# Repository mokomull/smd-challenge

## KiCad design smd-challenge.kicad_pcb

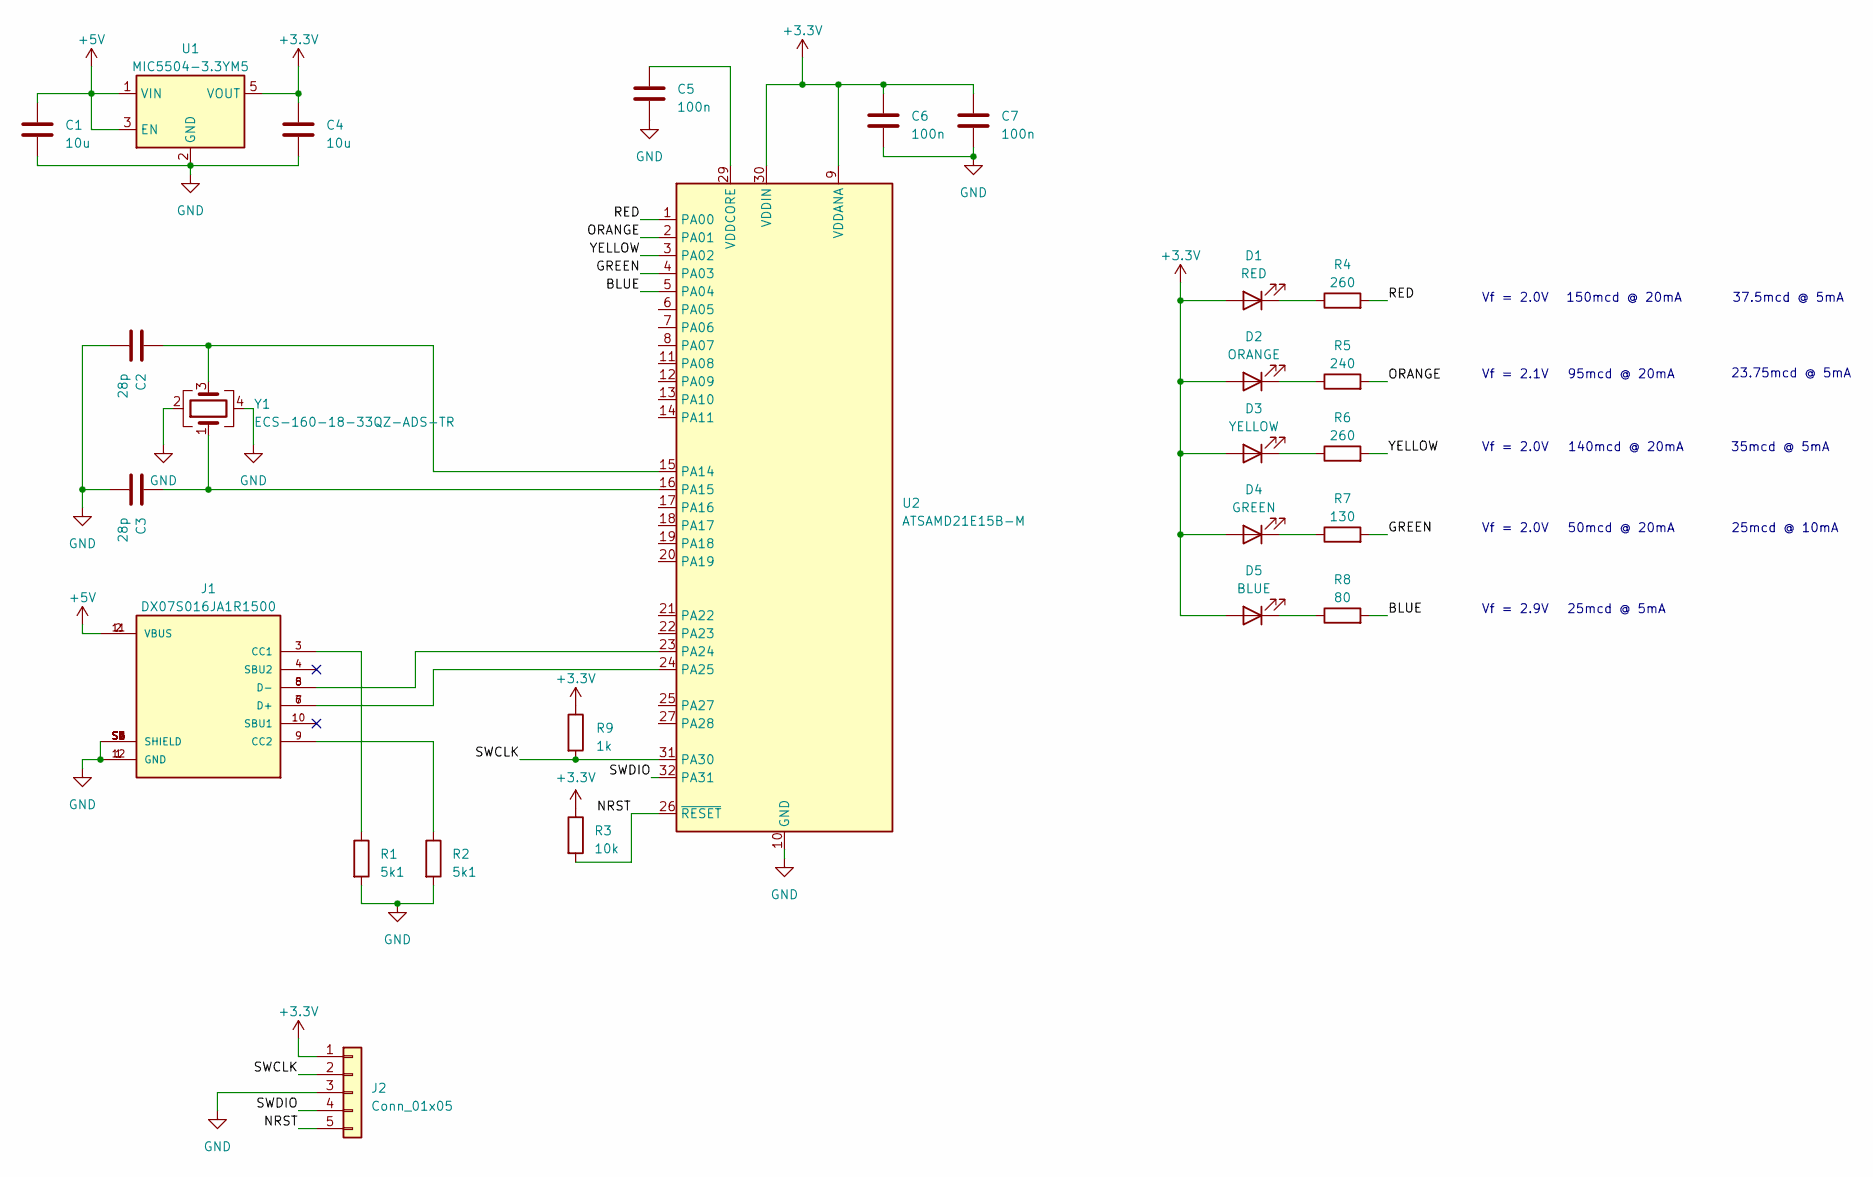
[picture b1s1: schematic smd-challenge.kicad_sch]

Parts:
C1, C4: 10u; C_1206_3216Metric; Digikey 1276-3100-1-ND
C2, C3: 28p; C_0603_1608Metric; Digikey 1276-1254-1-ND
C5, C6, C7: 100n; C_0603_1608Metric; Digikey 1276-1006-1-ND
D1: RED; LED_1206_3216Metric; Digikey 732-4991-1-ND
D2: ORANGE; LED_0805_2012Metric; Digikey 350-4355-1-ND
D3: YELLOW; LED_0603_1608Metric; Digikey 350-2032-1-ND
D4: GREEN; LED_0402_1005Metric; Digikey 732-11992-1-ND
D5: BLUE; LED_0201_0603Metric; Digikey 754-2022-1-ND
J1: DX07S016JA1R1500; JAE_DX07S016JA1R1500; PARTREV 1
J2: Conn_01x05; PinHeader_1x05_P2.54mm_Vertical_SMD_Pin1Left
R1, R2: 5k1; R_0603_1608Metric
R3: 10k; R_0603_1608Metric
R4: 260; R_1206_3216Metric; Digikey RMCF1206JT270RCT-ND
R5: 240; R_0805_2012Metric; Digikey RMCF0805JT240RCT-ND
R6: 260; R_0603_1608Metric; Digikey ‎RMCF0603JT270RCT-ND‎
R7: 130; R_0402_1005Metric; Digikey RMCF0402JT130RCT-ND
R8: 80; R_0201_0603Metric; Digikey P80.6ABCT-ND
R9: 1k; R_0603_1608Metric
U1: MIC5504-3.3YM5; SOT-23-5
U2: ATSAMD21E15B-M; QFN-32-1EP_5x5mm_P0.5mm_EP3.6x3.6mm
Y1: ECS-160-18-33QZ-ADS-TR; Crystal_SMD_SeikoEpson_FA238-4Pin_3.2x2.5mm

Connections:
+3V3: C4.1, C6.1, C7.1, D1.2 (A), D2.2 (A), D3.2 (A), D4.2 (A), D5.2 (A), J2.1, R3.1, R9.1, U1.5 (VOUT), U2.9 (VDDANA), U2.30 (VDDIN)
+5V: C1.1, J1.2 (VBUS), J1.11 (VBUS), U1.1 (VIN), U1.3 (EN)
/BLUE: R8.2, U2.5 (PA04)
/GREEN: R7.2, U2.4 (PA03)
/NRST: J2.5, R3.2, U2.26 (~RESET)
/ORANGE: R5.2, U2.2 (PA01)
/RED: R4.2, U2.1 (PA00)
/SWCLK: J2.2, R9.2, U2.31 (PA30)
/SWDIO: J2.4, U2.32 (PA31)
/YELLOW: R6.2, U2.3 (PA02)
GND: C1.2, C2.2, C3.2, C4.2, C5.2, C6.2, C7.2, J1.1 (GND), J1.12 (GND), J1.S1 (SHIELD), J1.S2 (SHIELD), J1.S3 (SHIELD), J1.S4 (SHIELD), J1.S5 (SHIELD), J1.S6 (SHIELD), J2.3, R1.2, R2.2, U1.2 (GND), U2.10 (GND), U2.28 (GND), Y1.2, Y1.4
unnamed: C2.1, U2.15 (PA14), Y1.3
unnamed: C3.1, U2.16 (PA15), Y1.1
unnamed: C5.1, U2.29 (VDDCORE)
unnamed: D1.1 (K), R4.1
unnamed: D2.1 (K), R5.1
unnamed: D3.1 (K), R6.1
unnamed: D4.1 (K), R7.1
unnamed: D5.1 (K), R8.1
unnamed: J1.3 (CC1), R1.1
unnamed: J1.5 (D-), J1.8 (D-), U2.23 (PA24)
unnamed: J1.6 (D+), J1.7 (D+), U2.24 (PA25)
unnamed: J1.9 (CC2), R2.1

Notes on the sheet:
Vf = 2.0V
Vf = 2.1V
Vf = 2.9V
25mcd @ 5mA
95mcd @ 20mA
50mcd @ 20mA
150mcd @ 20mA
140mcd @ 20mA
35mcd @ 5mA
25mcd @ 10mA
37.5mcd @ 5mA
23.75mcd @ 5mA

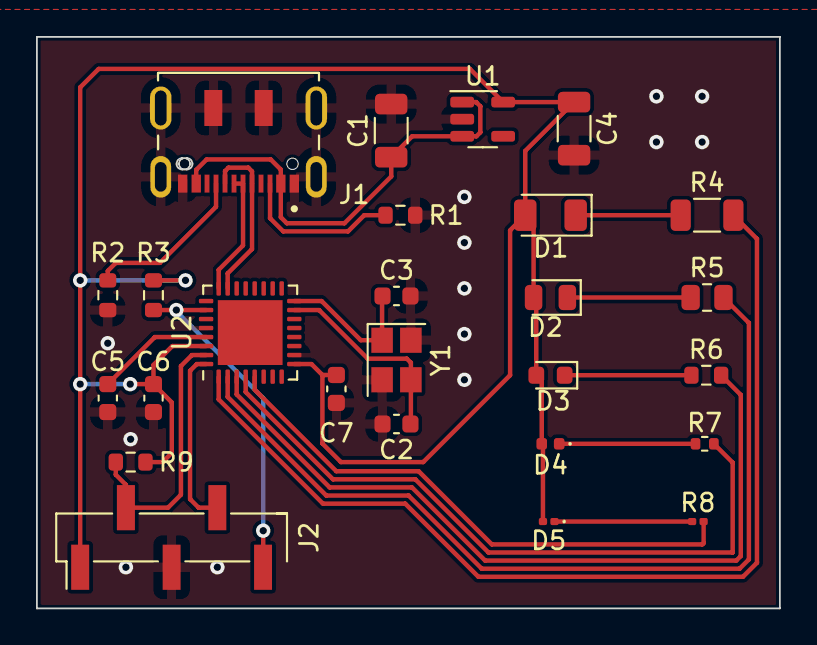
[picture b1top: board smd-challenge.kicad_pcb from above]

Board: 2 copper layers, 41.3 x 31.8 mm, 26 parts (0 on the bottom side), 23 nets.

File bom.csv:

"Source:","/home/mmullins/projects/smd-challenge/smd-challenge.kicad_sch"
"Date:","Wed 24 Mar 2021 08:59:18 PM PDT"
"Tool:","Eeschema (5.99.0-9795-gc3c3649211)"
"Generator:","/home/mmullins/Downloads/kicad/usr/share/kicad/plugins/bom_csv_grouped_by_value.py"
"Component Count:","26"

"Individual Components:"

"Item","Qty","Reference(s)","Value","LibPart","Footprint","Datasheet","Digikey","MANUFACTURER","MAXIMUM_PACKAGE_HEIGHT","PARTREV","STANDARD"
"","","C1","10u","Device:C","Capacitor_SMD:C_1206_3216Metric","~","1276-3100-1-ND","","","",""
"","","C2","12p","Device:C","Capacitor_SMD:C_0603_1608Metric","~","1276-1254-1-ND","","","",""
"","","C3","12p","Device:C","Capacitor_SMD:C_0603_1608Metric","~","1276-1254-1-ND","","","",""
"","","C4","10u","Device:C","Capacitor_SMD:C_1206_3216Metric","~","1276-3100-1-ND","","","",""
"","","C5","100n","Device:C","Capacitor_SMD:C_0603_1608Metric","~","1276-1006-1-ND","","","",""
"","","C6","100n","Device:C","Capacitor_SMD:C_0603_1608Metric","~","1276-1006-1-ND","","","",""
"","","C7","100n","Device:C","Capacitor_SMD:C_0603_1608Metric","~","1276-1006-1-ND","","","",""
"","","D1","RED","Device:LED","LED_SMD:LED_1206_3216Metric","~","732-4991-1-ND","","","",""
"","","D2","ORANGE","Device:LED","LED_SMD:LED_0805_2012Metric","~","350-4355-1-ND","","","",""
"","","D3","YELLOW","Device:LED","LED_SMD:LED_0603_1608Metric","~","350-2032-1-ND","","","",""
"","","D4","GREEN","Device:LED","LED_SMD:LED_0402_1005Metric","~","732-11992-1-ND","","","",""
"","","D5","BLUE","Device:LED","LED_SMD:LED_0201_0603Metric","~","754-2022-1-ND","","","",""
"","","J1","DX07S016JA1R1500","USBConn:DX07S016JA1R1500","USBConn6:JAE_DX07S016JA1R1500","","","JAE Industry Ltd.","3.31 mm","1","Manufacturer Recommendations"
"","","J2","Conn_01x05","Connector_Generic:Conn_01x05","Connector_PinHeader_2.54mm:PinHeader_1x05_P2.54mm_Vertical_SMD_Pin1Left","~","","","","",""
"","","R1","5k1","Device:R","Resistor_SMD:R_0603_1608Metric","~","","","","",""
"","","R2","5k1","Device:R","Resistor_SMD:R_0603_1608Metric","~","","","","",""
"","","R3","10k","Device:R","Resistor_SMD:R_0603_1608Metric","~","","","","",""
"","","R4","260","Device:R","Resistor_SMD:R_1206_3216Metric","~","RMCF1206JT270RCT-ND","","","",""
"","","R5","240","Device:R","Resistor_SMD:R_0805_2012Metric","~","RMCF0805JT240RCT-ND","","","",""
"","","R6","260","Device:R","Resistor_SMD:R_0603_1608Metric","~"," ‎RMCF0603JT270RCT-ND‎ ","","","",""
"","","R7","130","Device:R","Resistor_SMD:R_0402_1005Metric","~","RMCF0402JT130RCT-ND","","","",""
"","","R8","80","Device:R","Resistor_SMD:R_0201_0603Metric","~","P80.6ABCT-ND","","","",""
"","","R9","1k","Device:R","Resistor_SMD:R_0603_1608Metric","~","","","","",""
"","","U1","MIC5504-3.3YM5","Regulator_Linear:MIC5504-3.3YM5","Package_TO_SOT_SMD:SOT-23-5","http://ww1.microchip.com/downloads/en/DeviceDoc/MIC550X.pdf","","","","",""
"","","U2","ATSAMD21E15B-M","MCU_Microchip_SAMD:ATSAMD21E15B-M","Package_DFN_QFN:QFN-32-1EP_5x5mm_P0.5mm_EP3.6x3.6mm","http://ww1.microchip.com/downloads/en/DeviceDoc/SAM_D21_DA1_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","","","","",""
"","","Y1","FA-238 16.0000MB-K3","Device:Crystal_GND24","Crystal:Crystal_SMD_SeikoEpson_FA238-4Pin_3.2x2.5mm","~","","","","",""



"Collated Components:"

"Item","Qty","Reference(s)","Value","LibPart","Footprint","Datasheet","Digikey","MANUFACTURER","MAXIMUM_PACKAGE_HEIGHT","PARTREV","STANDARD"
"1","2","C1, C4","10u","Device:C","Capacitor_SMD:C_1206_3216Metric","~","1276-3100-1-ND","","","",""
"2","2","C2, C3","12p","Device:C","Capacitor_SMD:C_0603_1608Metric","~","1276-1254-1-ND","","","",""
"3","3","C5, C6, C7","100n","Device:C","Capacitor_SMD:C_0603_1608Metric","~","1276-1006-1-ND","","","",""
"4","1","D1","RED","Device:LED","LED_SMD:LED_1206_3216Metric","~","732-4991-1-ND","","","",""
"5","1","D2","ORANGE","Device:LED","LED_SMD:LED_0805_2012Metric","~","350-4355-1-ND","","","",""
"6","1","D3","YELLOW","Device:LED","LED_SMD:LED_0603_1608Metric","~","350-2032-1-ND","","","",""
"7","1","D4","GREEN","Device:LED","LED_SMD:LED_0402_1005Metric","~","732-11992-1-ND","","","",""
"8","1","D5","BLUE","Device:LED","LED_SMD:LED_0201_0603Metric","~","754-2022-1-ND","","","",""
"9","1","J1","DX07S016JA1R1500","USBConn:DX07S016JA1R1500","USBConn6:JAE_DX07S016JA1R1500","","","JAE Industry Ltd.","3.31 mm","1","Manufacturer Recommendations"
"10","1","J2","Conn_01x05","Connector_Generic:Conn_01x05","Connector_PinHeader_2.54mm:PinHeader_1x05_P2.54mm_Vertical_SMD_Pin1Left","~","","","","",""
"11","2","R1, R2","5k1","Device:R","Resistor_SMD:R_0603_1608Metric","~","","","","",""
"12","1","R3","10k","Device:R","Resistor_SMD:R_0603_1608Metric","~","","","","",""
"13","1","R4","260","Device:R","Resistor_SMD:R_1206_3216Metric","~","RMCF1206JT270RCT-ND","","","",""
"14","1","R5","240","Device:R","Resistor_SMD:R_0805_2012Metric","~","RMCF0805JT240RCT-ND","","","",""
"15","1","R6","260","Device:R","Resistor_SMD:R_0603_1608Metric","~"," ‎RMCF0603JT270RCT-ND‎ ","","","",""
"16","1","R7","130","Device:R","Resistor_SMD:R_0402_1005Metric","~","RMCF0402JT130RCT-ND","","","",""
"17","1","R8","80","Device:R","Resistor_SMD:R_0201_0603Metric","~","P80.6ABCT-ND","","","",""
"18","1","R9","1k","Device:R","Resistor_SMD:R_0603_1608Metric","~","","","","",""
"19","1","U1","MIC5504-3.3YM5","Regulator_Linear:MIC5504-3.3YM5","Package_TO_SOT_SMD:SOT-23-5","http://ww1.microchip.com/downloads/en/DeviceDoc/MIC550X.pdf","","","","",""
"20","1","U2","ATSAMD21E15B-M","MCU_Microchip_SAMD:ATSAMD21E15B-M","Package_DFN_QFN:QFN-32-1EP_5x5mm_P0.5mm_EP3.6x3.6mm","http://ww1.microchip.com/downloads/en/DeviceDoc/SAM_D21_DA1_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","","","","",""
"21","1","Y1","FA-238 16.0000MB-K3","Device:Crystal_GND24","Crystal:Crystal_SMD_SeikoEpson_FA238-4Pin_3.2x2.5mm","~","","","","",""

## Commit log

2021-03-19 Start of a design.
2021-03-19 Swap crystal for something smaller; settle on layout
2021-03-19 Layout with the SAMD21.
    The only thing I really don't like is the snakey 3.3V rail but since I
    can stitch the grounds back together via the B.Cu zone, it's mostly
    fine.
2021-03-22 Pick parts for LEDs, values for resistors
2021-03-22 Pick Digikey part numbers for more things
2021-03-22 PCB: swap through-hole for SMD header
2021-03-22 PCB: nudge one trace over for better GND connectivity
2021-03-24 Add pull-up resistor on SWCLK per Microchip docs
2021-03-25 Nudge the USB connector closer to the edge of the board so it's possible to plug in, and adjust some traces for symmetry
2021-03-25 Add text to the back layer.
2021-03-25 Label the LEDs by color
2021-03-25 Swap crystal (and load caps) for what's in stock at Mouser
2021-03-25 /NRST should be connected to a pull-UP
2021-05-04 Fabrication output from initial run
    This was built at Aisler and populated with parts from Mouser.
2021-05-04 Initial stab at some firmware.
    This mostly is a copy of the instructions at
    https://github.com/rust-embedded/cortex-m-quickstart. It does produce
    an ELF file with instructions in it!
    The OpenOCD config seems to work for reading CPU registers and stuff,
    but goes completely bonkers when I run the `load` GDB command.
2021-05-04 firmware: blink the red LED
    This actually loads onto the target device with the Black Magic firmware
    and runs fine!
2021-05-04 firmware: flash all the LEDs
    Not sure what makes my brain hurt more:
    (a) all this &mut dyn indirection, or
    (b) staring straight into the LEDs themselves
2021-05-06 fw: enable XOSC unconditionally
    This gets a nice 16MHz sine wave, probed at C2 and C3.
    "ondemand" was a surprise; the chip tries to be smart and enables the
    oscillator only when selected as a source for a GCLK, but I'm not quite
    ready for that yet.
2021-05-06 fw: try to enable TCC2
    It does not work, at all. COUNT is always reading out as zeroes.
2021-05-06 fw: use OSC8M to clock the timer
    This is the clock we get by default when we use with_internal_8mhz(),
    and DFLL48M is disabled by default.
    This outputs a 997Hz, 50% duty cycle square wave on the red LED.
2021-05-06 fw: use XOSC as the timer clock source
    This is a 16MHz crystal, so with /2 division it'll work exactly as
    before.
    This resulted in "1.00000kHz" as reported by the SDS 1104X-E, which is
    absolutely more precise than I expected it to be.
2021-05-06 fw: invert polarity, reduce brightness
    Idling the pin high means the LED idles *off*; this in turn means that
    "bigger number in the cc register means brighter".
    Even 50% duty cycle for this LED is way too bright, so turn that down a
    smidge.
2021-05-06 fw: generate 48MHz using the onboard FDPLL
    I intentionally left the CC register set low, because even
    2_000/48_000 = 4.1% duty cycle is plenty bright for this LED.
2021-05-08 fw: instantiate a USB device
    Once again, I built something that doesn't seem to work :(
    As far as I can tell, not even the D+ pull-up is enabled, and the host
    PC still doesn't know anything is connected to the port.
    (edit 3 days later: seems to have been a layer 1 problem, where the side
    of the MCU with D+ and D- pins didn't really get soldered down well. A
    bit of reflow and it's working fine now.)
2021-05-08 fw: first stab at USB HID
    This is detected as a USB HID device by Linux, but doesn't actually show
    up in /sys/class/leds at all.
    This results in a seemingly reasonable device/interface/report
    descriptor:
    Bus 001 Device 111: ID 1337:4209 Matt Mullins smd-challenge
    Device Descriptor:
2021-05-08 fw: tweak USB HID descriptor a bit
    The Application collection needed to be a "Generic Desktop - Keyboard"
    usage (which is usage type "CA" in the HID Usage Tables).
    This results in:
    Report Descriptor: (length is 25)
    Item(Global): Usage Page, data= [ 0x01 ] 1
    Generic Desktop Controls
2021-05-09 fw: make my own HID report descriptor
    The macro language doesn't seem to be flexible enough to define
    repetitive bitfields, so write it by hand. This seems to parse
    correctly, but still doesn't give me multiple LED objects in Linux.
2021-05-09 fw: use arbitrary LED IDs
    compose, kana, sleep, suspend, and mail all seem to default to the
    "none" trigger in Linux, and at least lets me distinguish them in
    /sys/class/leds. With wireshark, this seems to transmit the OUT reports
    I expect, too (i.e. compose is the least-significant bit, mail is the
    most-significant bit).
2021-05-09 fw: turn on orange LED via USB
    This is on the TCC2 timer as well, so it's pretty straightforward.
2021-05-09 fw: use GPIO for yellow, green, and blue
    TCC3 doesn't exist at all on the SAMD21E15B, so I don't have any PWM
    options for these three colors. So they're going to be crazy bright,
    but most importantly: THEY WORK!
2021-05-09 fw: use plain GPIO for all LEDs
    Since I don't have a timer that is usable for PWM on three of the five
    LEDs, use plain GPIO for all of them. This is incredibly bright, but
    it's consistent.
2021-05-09 Add udev rules that match the USB device.
    This actually works every time I plug the device in!
2021-10-26 cargo update
2021-10-26 fw: port to ATSAME51J-based board
    Major differences from the SAM D21 code:
    * The D51-series doesn't have an 8MHz internal clock, instead, only a
    32K that the HAL configures to multiply up to 120MHz to run the CPU
    clock.
    * The oscillator configuration is in OSCCTRL now, not SYSCTRL.
    * The DPLLs must output at least 96MHz, so I've chosen to have them
2021-10-26 fw: adjust GPIO assignments for dsp-dev-board
    This board also put the LEDs as positive-logic, so invert that behavior.
2021-10-26 fw: use atsamd_hal v2 GPIO API
    This cleans up a whole lot of deprecation warnings.

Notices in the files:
smd-challenge.kicad_pcb:
© 2021 Matt Mullins
